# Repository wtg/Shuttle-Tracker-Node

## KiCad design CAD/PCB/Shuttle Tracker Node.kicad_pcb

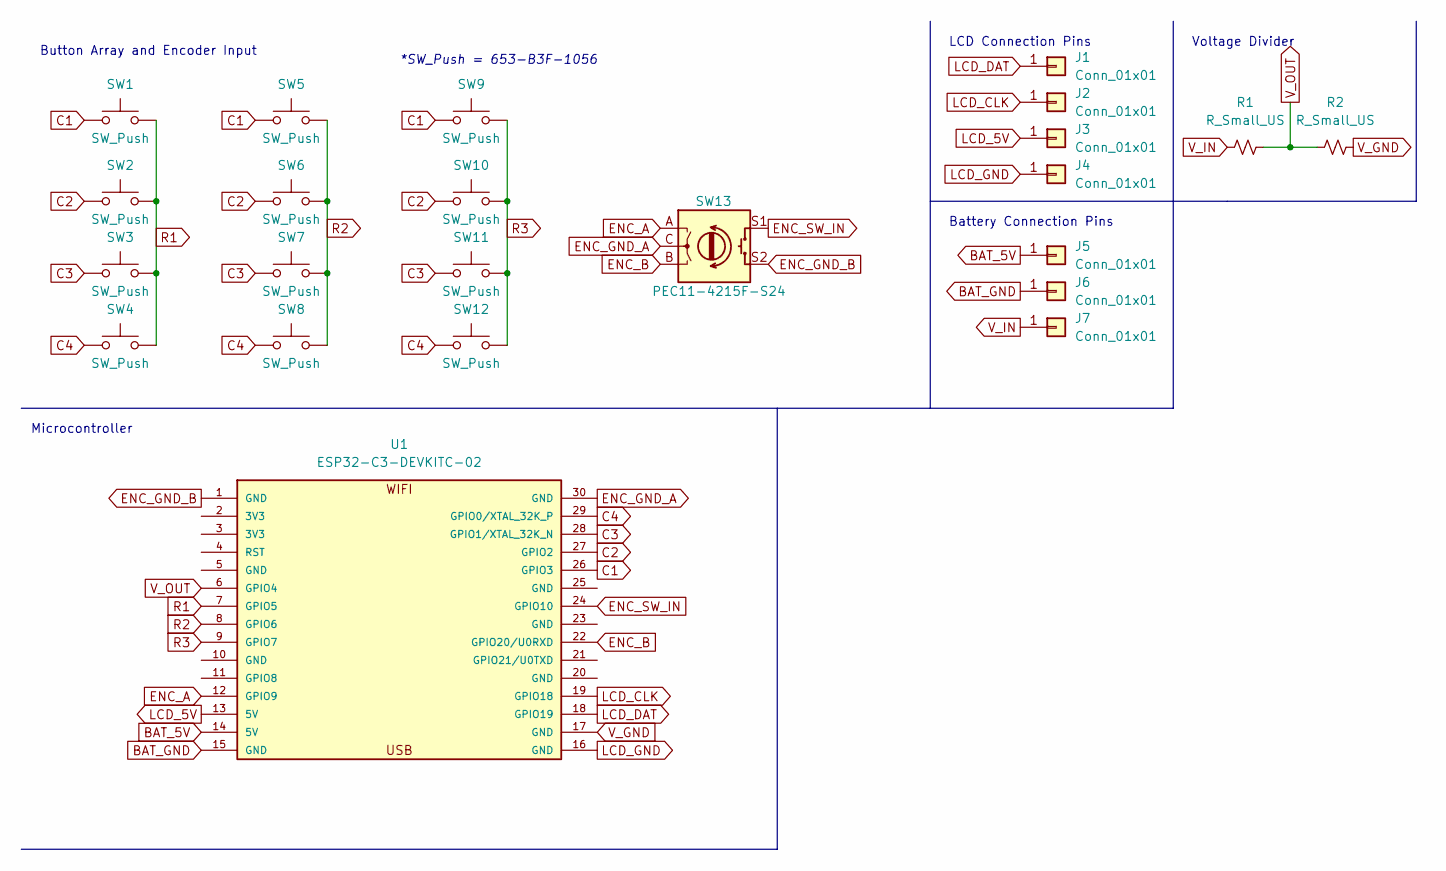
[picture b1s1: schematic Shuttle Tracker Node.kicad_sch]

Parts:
J1, J2, J3, J4, J5, J6, J7: Conn_01x01; Pin_D1.0mm_L10.0mm
R1, R2: R_Small_US; R_Axial_DIN0204_L3.6mm_D1.6mm_P5.08mm_Horizontal
SW1, SW2, SW3, SW4, SW5, SW6, SW7, SW8, SW9, SW10, SW11, SW12: SW_Push; B3F-1056
SW13: PEC11-4215F-S24; PEC11R-4215F-S0024
U1: ESP32-C3-DEVKITC-02; XCVR_ESP32-C3-DEVKITC-02

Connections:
BAT_5V: J5.1, U1.14 (5V)
BAT_GND: J6.1, U1.15 (GND)
C1: SW1.1, SW5.1, SW9.1, U1.26 (GPIO3)
C2: SW2.1, SW6.1, SW10.1, U1.27 (GPIO2)
C3: SW3.1, SW7.1, SW11.1, U1.28 (GPIO1/XTAL_32K_N)
C4: SW4.1, SW8.1, SW12.1, U1.29 (GPIO0/XTAL_32K_P)
ENC_A: SW13.A, U1.12 (GPIO9)
ENC_B: SW13.B, U1.22 (GPIO20/U0RXD)
ENC_GND_A: SW13.C, U1.30 (GND)
ENC_GND_B: SW13.S2, U1.1 (GND)
ENC_SW_IN: SW13.S1, U1.24 (GPIO10)
LCD_5V: J3.1, U1.13 (5V)
LCD_CLK: J2.1, U1.19 (GPIO18)
LCD_DAT: J1.1, U1.18 (GPIO19)
LCD_GND: J4.1, U1.16 (GND)
R1: SW1.2, SW2.2, SW3.2, SW4.2, U1.7 (GPIO5)
R2: SW5.2, SW6.2, SW7.2, SW8.2, U1.8 (GPIO6)
R3: SW9.2, SW10.2, SW11.2, SW12.2, U1.9 (GPIO7)
V_GND: R2.2, U1.17 (GND)
V_IN: J7.1, R1.1
V_OUT: R1.2, R2.1, U1.6 (GPIO4)

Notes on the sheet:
Microcontroller
*SW_Push = 653-B3F-1056
Voltage Divider
Button Array and Encoder Input
Battery Connection Pins
LCD Connection Pins

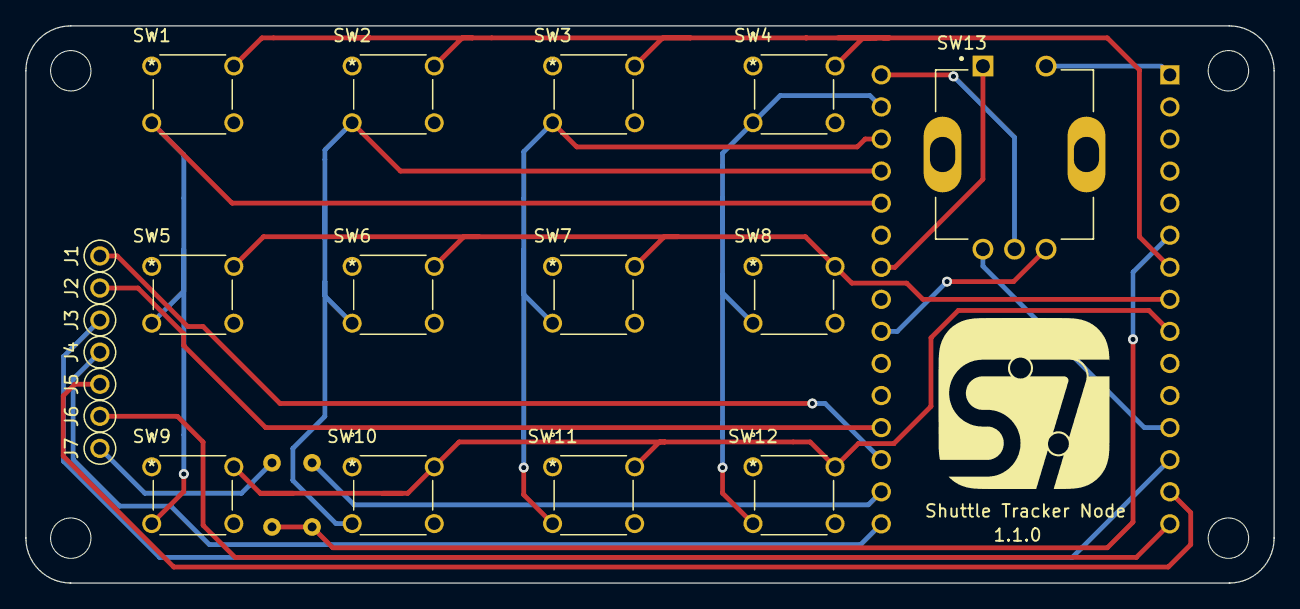
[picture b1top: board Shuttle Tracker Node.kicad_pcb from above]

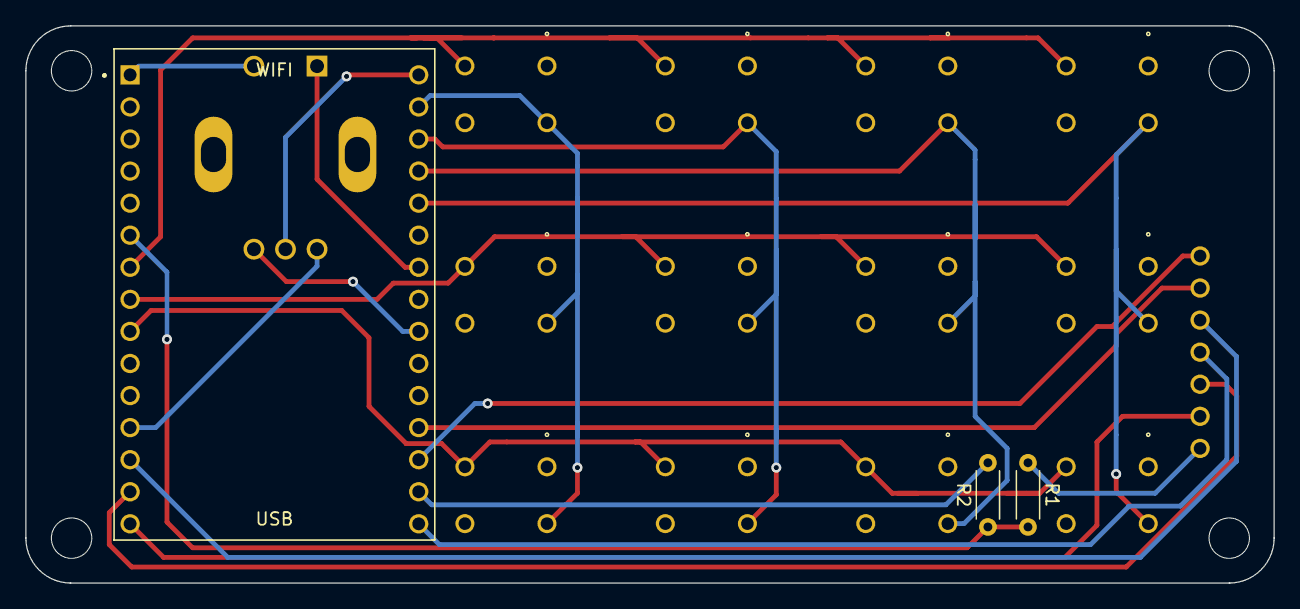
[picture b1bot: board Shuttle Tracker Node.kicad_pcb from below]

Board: 2 copper layers, 98.9 x 44.1 mm, 23 parts (3 on the bottom side), 21 nets.

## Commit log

2022-09-30 Initial code
2022-10-25 RGB_Shield_Display
    It is a basic code to use the mono-shield display.
2022-10-25 Mono-chrome display code
    This code uses Adafruit_RGBLCDShield library, and it also works properly with the ESP 32 board
2022-10-25 Move files to prototyping directory
2022-10-25 Keypad button testing
2022-11-01 Preliminary menu structure
2022-11-29 Preliminary wiring diagram
2022-12-10 Create I2C-Scanner
    This is the code to find the address of I2C device that is connected with a board.
2022-12-10 Update Display
2022-12-10 Code for testing with display and iBeacon
2023-01-28 Add CAD files
2023-01-28 Reorganize files
2023-02-02 Encoder prototypes, one ready for use(ish)
2023-02-07 Added support for encoder push button prototype
2023-02-07 Updated CAD files to current prototype
2023-02-08 moved hole position to top
2023-02-10 Create iBeacon+Display+Power_Level
    BLE power level is modified
2023-02-10 Rename iBeacon+Display+Power_Level to iBeacon+Display+Power_Level.ino
2023-02-10 Finished PCB Schematic
2023-02-10 update CAD for 2/10 meeting
2023-02-11 Converted button matrix code to interrupt paradigm.
    Needs to be tested once we have dev board for button matrix
2023-02-14 Place Components on PCB
2023-02-14 Finished PCB Routing
2023-02-14 Added Silkscreen
2023-02-15 fixed keypad const array from string to char
2023-02-17 testing with buttons
2023-02-17 PCB Routing Updates
2023-02-17 reorganized prototype files
2023-02-17 Updated keycap tolerances and font style
2023-02-17 added power button
2023-02-21 Added Mounting Holes
2023-02-21 Changed IO Configuration
2023-02-21 Untrack and ignore fp-info-cache
2023-02-22 Changed location of mounting holes
2023-02-22 Fixed side of board not being straight
2023-02-22 Fixed trace and mounting hole overlap
2023-02-24 re-organization
2023-02-24 Working on interrupt keypad.
    needs work on pin assignment, Currently has chaotic behavior.
2023-02-24 Created Makefile
2023-02-24 Fixed typo
2023-02-24 bouncing value updates on interrupt.
2023-02-27 Tweaking keypad.
2023-02-28 Add fabrication files
2023-02-28 Switched to a polling paradigm.
    Interrupt based keypad wasnt working. For now we should stick to polling.
2023-02-28 Initial menu navigation with encoder
2023-02-28 Compile, Upload, and Monitor with one make command
2023-02-28 Added bouncing to the encoder
2023-02-28 Changed Display File Names
2023-02-28 updated backplate and reorginized PCB assembly update
2023-03-03 Begun work on dev environment guide.
2023-03-04 include symlink instruction.
2023-03-14 Finilzed Cad Model for PCB
2023-03-17 Initial final firmware with display state and class structure
2023-03-18 Create OTA_Testing(RPI)
2023-03-18 Create ESP_MAC_Address
2023-03-18 Updated pin configuration for buttons
2023-03-18 Updated pin congifuration again
2023-03-18 updated (hopefully) final case design
2023-03-19 Add serial command interface to emulate keypad and encoder
2023-03-19 Display bugfixes
2023-03-19 Serial commands fix
2023-03-19 Misc cleanup
2023-03-19 Add backlight timeout
2023-03-19 Add battery measurement
2023-03-19 Update fabrication files
2023-03-19 Add beacon
2023-03-19 Fix cursor and change Bluetooth off message
2023-03-24 Updated spacing for pins
2023-03-24 updated pin configuration for encoder
2023-03-24 Silkscreen updates
2023-03-24 Set pin assignments to match schematic, adjust resistor value
2023-03-24 Added rudimentary keypad to firmware.
2023-03-24 Updated size of connector pads
2023-03-25 Changed Logo
2023-03-25 Update logo
2023-03-26 Reorganized keypad polling into its own function.
2023-03-26 Resets busID when entring new busId.
2023-03-26 Added new makefile option for production
    Disables unecesasry serial printing
2023-04-01 Update OTA_Testing(RPI)
2023-04-07 Boot directly to bus entry screen
2023-04-07 Added Files
2023-04-07 Added library for storing data in memory.
    Reads busID from memory on startup, updates on busID change. Needs testings.
2023-04-11 updated to latest .stl
2023-04-11 Reorganized and commented persistant changes.
2023-04-14 Bluetooth Slimming
2023-04-18 Change beacon interval to 1 second
2023-09-19 Changed the menu structure
2023-09-19 adding elements for a better battery algorithm
2023-09-24 add sanity check and event driven update inside the battery loop
2023-09-24 new battery algorithm
2023-09-29 test commit
2023-10-06 sketch version of OTA firmware update
2023-10-06 fixing battery accuracy
2023-10-07 create WifiManager for wifi set up
2023-10-07 the wifi stat from Display will print out the actual IP address
2023-10-13 the wifi will timeout 30s before trying to connect, then will try to connect for 30s again, if it cant found anything then it will wait for 1 hour until the next attempt
2023-10-13 Insertion of USB Update Porthole
    Constructed a hole and rearranged case layout to make it easier to update each node
2023-10-13 the wifi will try to connect for 3s, then timeout for 15s for now
2023-10-20 todo added
2023-10-27 broadcasting before having a busID with a generated MAC address
2023-10-27 fix broadcasting
2023-10-27 clean up
2023-10-31 Fixes the ibeacon no bus ID broadcast
    Initially it was setting the major with the device mac, changed to store mac in minor. Fixed major field not updating
2023-10-31 minor visual bug fixes
    Need to fix advertising interval
2023-11-03 added password O-o
2023-11-10 add the certificate for HTTPS
2023-11-10 Hole added
2023-11-10 G code for printing TWO cases
2024-02-09 binary files for update. only need firmware.ino.bin so far
2024-02-16 a hardcoded version for OTA update
2024-02-16 Version.txt with HTTPS
2024-02-23 TODO added, reminder for binary fetching
2024-03-01 report to system added
2024-03-22 Update the rootCAcertificate and the OTA firmware version check should be fully functioned
2024-03-22 create a new state for the navigation panel to show the current version of the node
2024-04-05 .bin binary
2024-04-05 .elf binary
2024-04-05 .map binary
2024-04-12 update rootCA function
2024-04-12 new root update
2024-04-16 set up the display for wifi connection
2024-04-16 set the display to blank, stop the user from interupting
2024-04-16 bug fixed for naming
2024-04-16 set function names in display.h
2025-06-06 add SIM800L+NEO6M_GPS schematic on ESP32 and add sending/recieve function on GPS to phone device
2025-06-06 create a Firebase database and publish long/lat to the server via SIM800L
2025-06-10 remove becon related codes, ready to add GPS+2G service.
2025-06-13 adding GPS through SIM onto the Node
2025-06-13 adding GPS via a server(firebase database for now) to the device
2025-06-13 fix error on defining GSM module
2025-06-27 unit testing for telemetryManager class
2025-06-27 move unit testing to unit_tests
2025-06-27 added README for unit tests
2025-06-27 rename telemetryManagerTestREADME->README since it will be a README for every unit tests
2025-07-11 refactor OTAupdate out of firmware.ino for further developing
2025-07-18 rename TelemetryManager_Test to TelemetryManagerTest to make it transparent with other tests
2025-07-18 Cmake for gtest
2025-07-18 unit test for OTA Firmware Update
